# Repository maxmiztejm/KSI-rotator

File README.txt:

Ksi-rotator is the 3D printed satellite tracking rotator.
Construction was inspired by Satnogs rotator.

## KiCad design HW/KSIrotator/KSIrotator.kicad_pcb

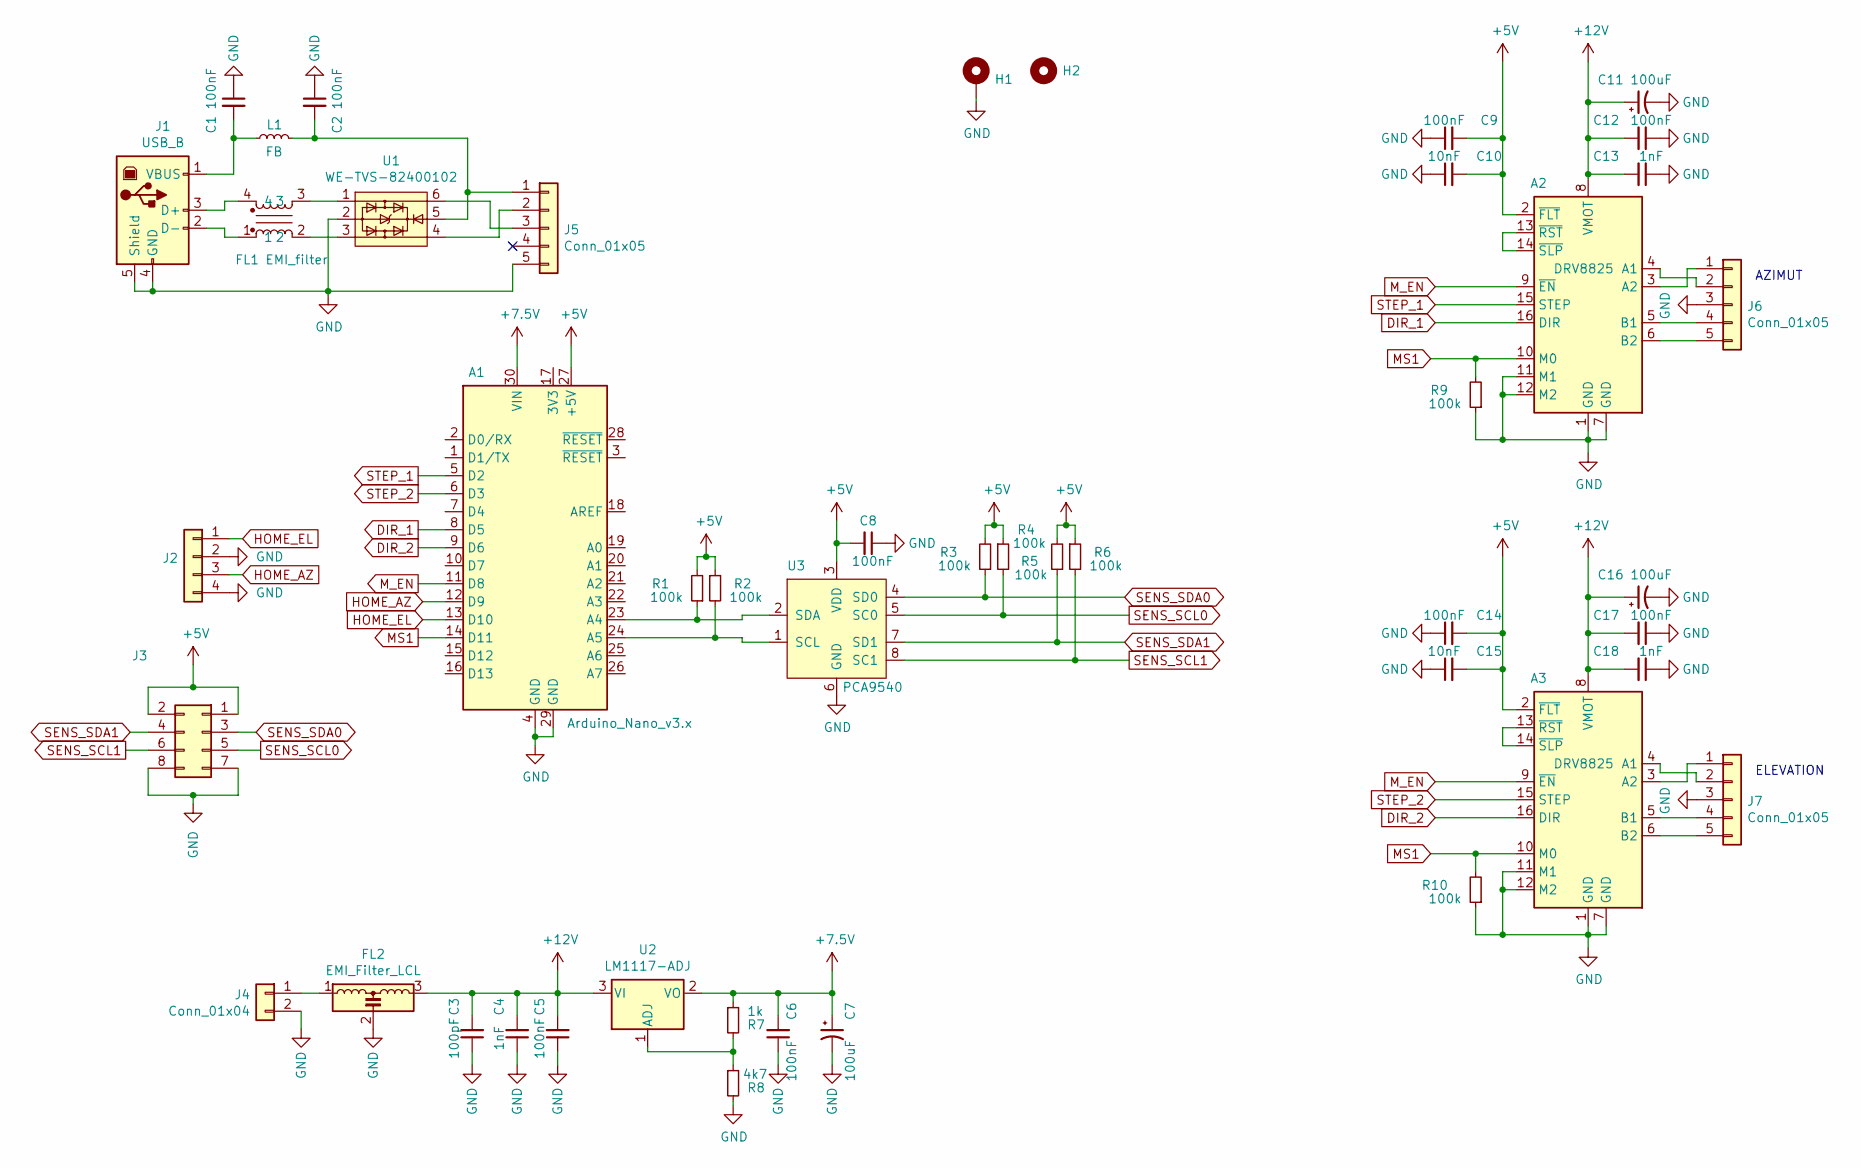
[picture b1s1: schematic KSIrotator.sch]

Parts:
A1: Arduino_Nano_v3.x; Arduino_Nano
A2, A3: DRV8825; Pololu_Breakout-16_15.2x20.3mm
C1, C2, C5, C6, C8, C9, C12, C14, C17: 100nF; C_0603_HS
C3: 100pF; C_0603_HS
C4, C13, C18: 1nF; C_0603_HS
C7, C11, C16: 100uF; CP_EIA-7361-438_AVX-U_Pad2.18x3.30mm_HandSolder
C10, C15: 10nF; C_0603_HS
FL1: EMI_filter; WE-CNSW_1812_HS
FL2: EMI_Filter_LCL; LC_1206_(3216)_HS
H1: MountingHole_Pad; MountingHole_3.2mm_M3_DIN965_Pad
H2: MountingHole; MountingHole_3.2mm_M3_DIN965
J1: USB_B; USB_B_OST_USB-B1HSxx_Horizontal
J2: Conn_01x05; PinHeader_1x04_P2.54mm_Vertical
J3: Conn_01x05; PinHeader_2x04_P2.54mm_Vertical
J4: Conn_01x04; BarrelJack_Wuerth_6941xx301002
J5: Conn_01x05; PinHeader_1x05_P2.00mm_Vertical
J6, J7: Conn_01x05; PhoenixContact_MSTBA_2,5_5-G-5,08_1x05_P5.08mm_Horizontal
L1: FB; R_0805_HS_b
R1, R2, R3, R4, R5, R6, R9, R10: 100k; R_0603_HS_b
R7: 1k; R_0603_HS_b
R8: 4k7; R_0603_HS_b
U1: WE-TVS-82400102; SOT-23-6
U2: LM1117-ADJ; SOT-223-3_TabPin2
U3: PCA9540; SOIC-8_5.23x5.23mm_P1.27mm

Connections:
+5V: A1.27 (+5V), A2.2 (~FLT), A3.2 (~FLT), C8.2, C9.2, C10.2, C14.2, C15.2, J3.1, J3.2, R1.2, R2.1, R3.2, R4.1, R5.2, R6.1, U3.3 (VDD)
+7.5V: A1.30 (VIN), C6.2, C7.1, R7.1, U2.2 (VO)
+12V: A2.8 (VMOT), A3.8 (VMOT), C3.2, C4.2, C5.2, C11.1, C12.2, C13.2, C16.1, C17.2, C18.2, FL2.3, U2.3 (VI)
DIR_1: A1.8 (D5), A2.16 (DIR)
DIR_2: A1.9 (D6), A3.16 (DIR)
GND: A1.4 (GND), A1.29 (GND), A2.1 (GND), A2.7 (GND), A2.11 (M1), A2.12 (M2), A3.1 (GND), A3.7 (GND), A3.11 (M1), A3.12 (M2), C1.1, C2.1, C3.1, C4.1, C5.1, C6.1, C7.2, C8.1, C9.1, C10.1, C11.2, C12.1, C13.1, C14.1, C15.1, C16.2, C17.1, C18.1, FL2.2, H1.1, J1.4 (GND), J1.5 (Shield), J2.2, J2.4, J3.7, J3.8, J4.2, J5.5, J6.3, J7.3, R8.2, R9.1, R10.1, U1.2, U3.6 (GND)
HOME_AZ: A1.12 (D9), J2.3
HOME_EL: A1.13 (D10), J2.1
MS1: A1.14 (D11), A2.10 (M0), A3.10 (M0), R9.2, R10.2
M_EN: A1.11 (D8), A2.9 (~EN), A3.9 (~EN)
unnamed: A1.23 (A4), R1.1, U3.2 (SDA)
unnamed: A1.24 (A5), R2.2, U3.1 (SCL)
unnamed: A2.3 (A2), J6.1
unnamed: A2.4 (A1), J6.2
unnamed: A2.5 (B1), J6.4
unnamed: A2.6 (B2), J6.5
unnamed: A2.13 (~RST), A2.14 (~SLP)
unnamed: A3.3 (A2), J7.1
unnamed: A3.4 (A1), J7.2
unnamed: A3.5 (B1), J7.4
unnamed: A3.6 (B2), J7.5
unnamed: A3.13 (~RST), A3.14 (~SLP)
unnamed: C1.2, J1.1 (VBUS), L1.1
unnamed: C2.2, J5.1, L1.2, U1.5
unnamed: FL1.1, J1.2 (D-)
unnamed: FL1.2, U1.3
unnamed: FL1.3, U1.1
unnamed: FL1.4, J1.3 (D+)
unnamed: FL2.1, J4.1
unnamed: J5.2, U1.4
unnamed: J5.3, U1.6
unnamed: R7.2, R8.1, U2.1 (ADJ)
SENS_SCL0: J3.5, R4.2, U3.5 (SC0)
SENS_SCL1: J3.6, R6.2, U3.8 (SC1)
SENS_SDA0: J3.3, R3.1, U3.4 (SD0)
SENS_SDA1: J3.4, R5.1, U3.7 (SD1)
STEP_1: A1.5 (D2), A2.15 (STEP)
STEP_2: A1.6 (D3), A3.15 (STEP)

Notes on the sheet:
AZIMUT
ELEVATION

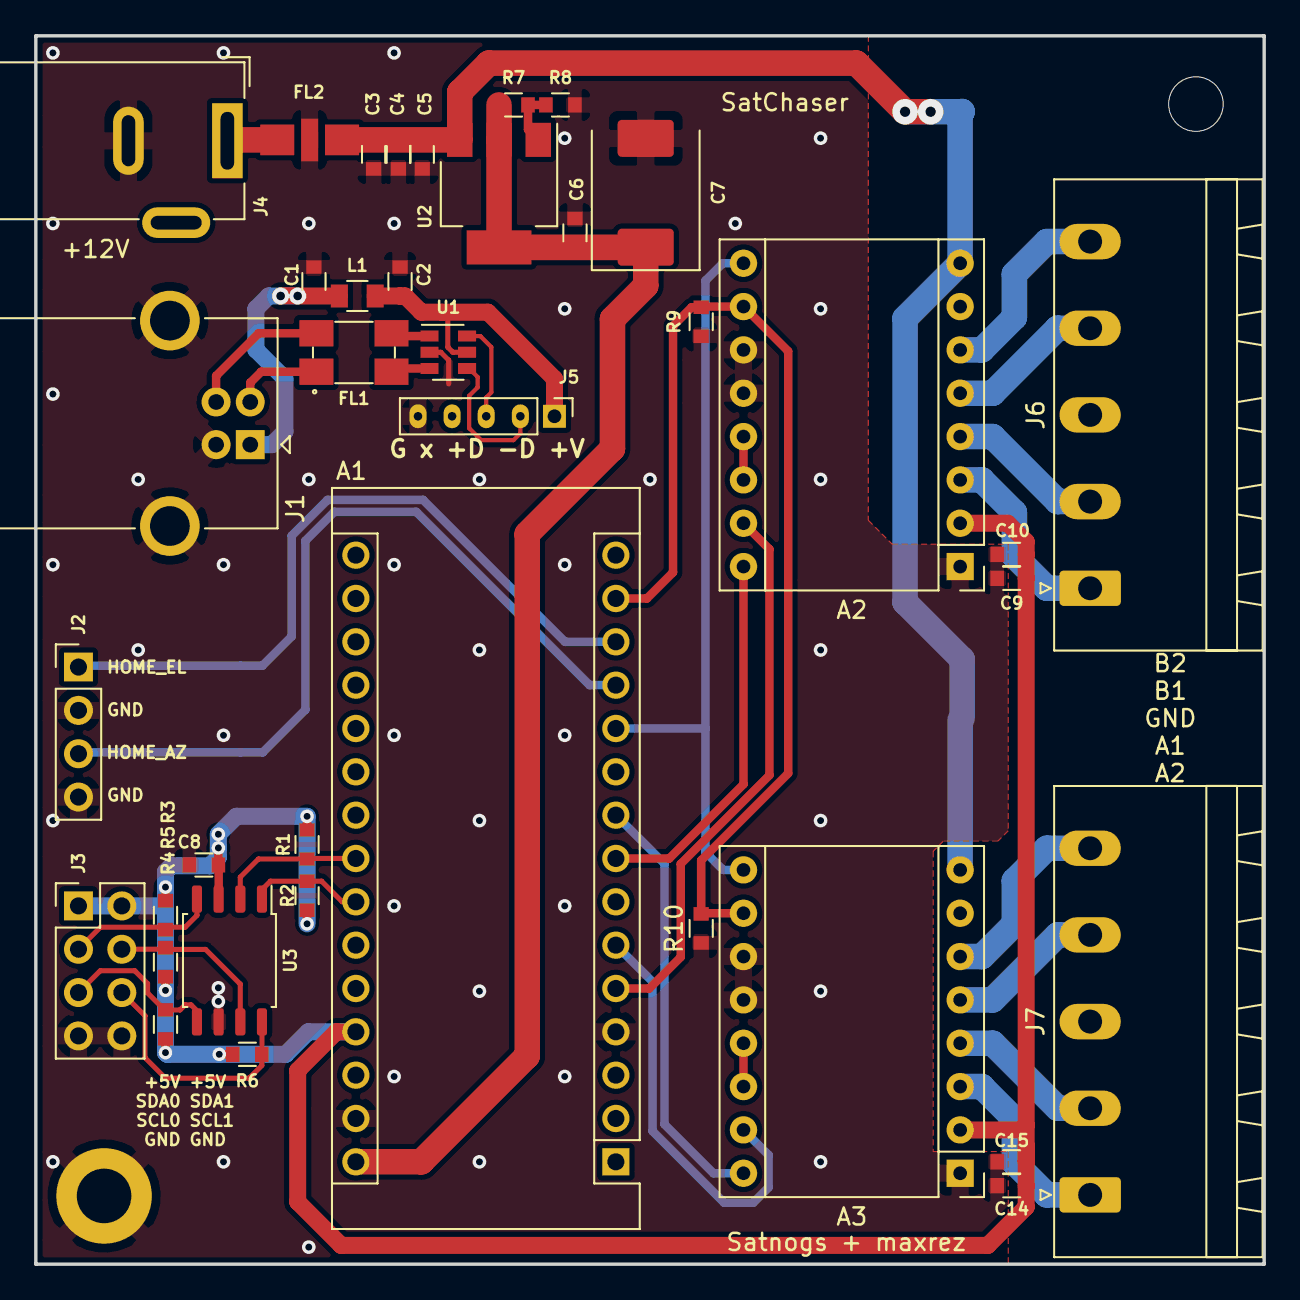
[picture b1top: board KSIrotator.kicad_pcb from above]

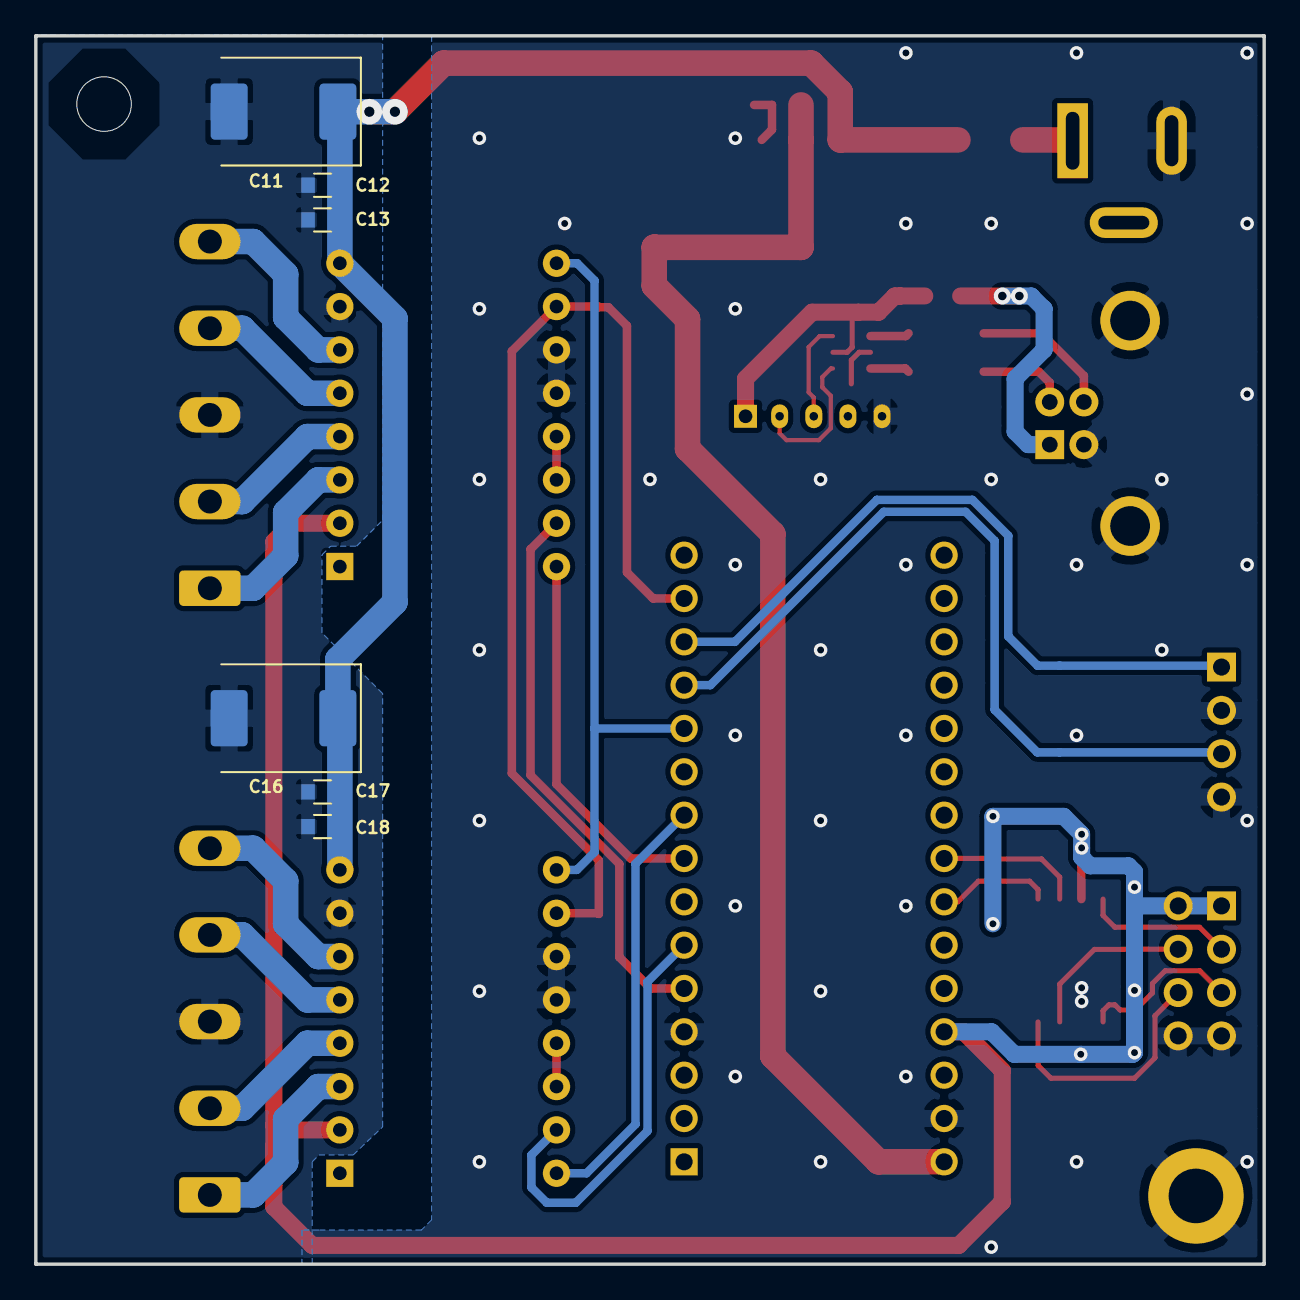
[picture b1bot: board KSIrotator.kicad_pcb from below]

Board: 2 copper layers, 72.0 x 72.0 mm, 46 parts (6 on the bottom side), 38 nets.

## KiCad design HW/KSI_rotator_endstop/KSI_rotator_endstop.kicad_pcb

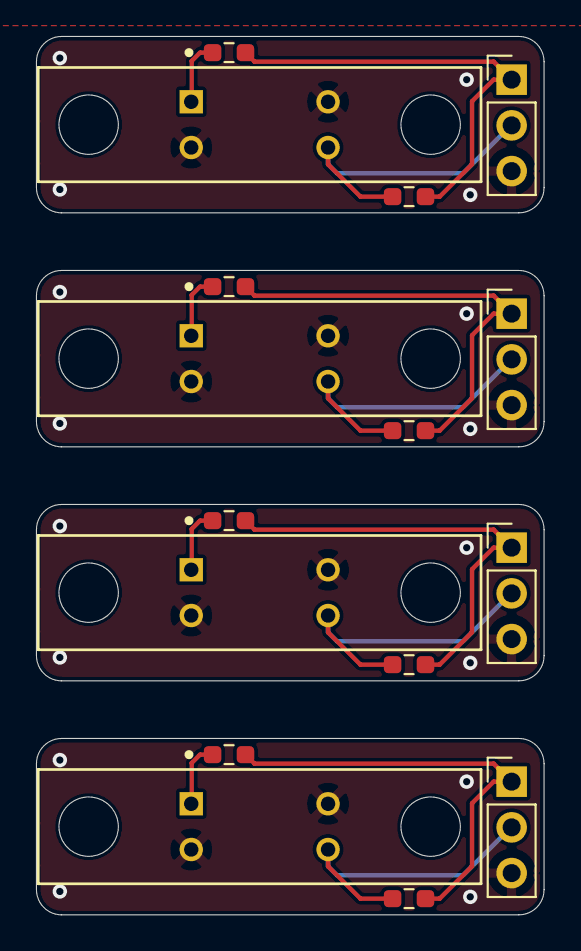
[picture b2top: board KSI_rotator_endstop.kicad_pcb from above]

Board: 2 copper layers, 28.2 x 48.8 mm, 16 parts (0 on the bottom side), 13 nets.

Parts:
J1, J2, J3, J4: Conn_01x03; PinHeader_1x03_P2.54mm_Vertical
R1, R3, R5, R6: 330; R_0603_1608Metric_Pad0.98x0.95mm_HandSolder
R2, R4, R7, R8: 10k; R_0603_1608Metric_Pad0.98x0.95mm_HandSolder
U1, U2, U3, U4: TCST2103; Vishay-TCST2300

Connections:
+3V3: J2.1, R3.2, R4.2
+5V: J1.1, R1.2, R2.2
GND: J1.3, J2.3, J3.3, J4.3, U1.2, U1.3, U2.2, U2.3, U3.2, U3.3, U4.2, U4.3
unnamed: R1.1, U1.1
unnamed: R3.1, U2.1
unnamed: R5.1, U3.1
unnamed: R6.1, U4.1
OUT1: J1.2, R2.1, U1.4
OUT2: J2.2, R4.1, U2.4
OUT3: J4.2, R8.1, U4.4
OUT4: J3.2, R7.1, U3.4
VCC: J4.1, R6.2, R8.2
VCCQ: J3.1, R5.2, R7.2

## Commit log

2023-04-10 add readme
2023-04-10 adding pictures
